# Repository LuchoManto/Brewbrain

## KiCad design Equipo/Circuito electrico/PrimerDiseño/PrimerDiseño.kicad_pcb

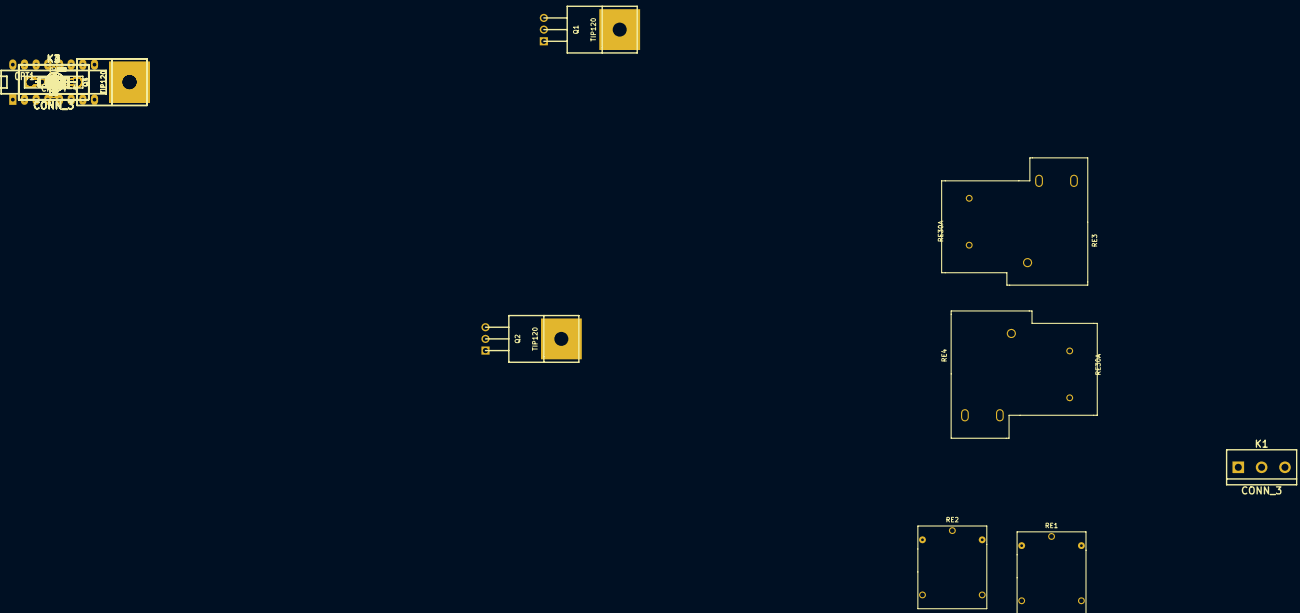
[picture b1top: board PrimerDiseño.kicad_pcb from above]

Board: 2 copper layers, 42 parts (0 on the bottom side), 31 nets, no tracks yet.

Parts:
D1, D2, D3, D4, D9, D10, D11, D12: LED; LED-3MM
D5, D6, D7, D8: DIODE; D3
K1, K2, K3, K4: CONN_3; bornier3
OPT1: CNY74-4; DIP-16__300_ELL
P1: CONN_5; PIN_ARRAY_5x1
Q1, Q2, Q3, Q4: TIP120; TO220
R1, R2, R3, R4: 50; R3
R5, R6, R7, R8: 470; R3
R9, R10, R11, R12, R15, R16, R17, R18: 1K; R3
RE1, RE2: RE
RE3, RE4: RE30A

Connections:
+5V: OPT1.10, OPT1.11, OPT1.14, OPT1.15
+12V: D5.2, D6.2, D7.2, D8.2, R15.1, R16.1, R17.1, R18.1
GND: D9.2, D10.2, D11.2, D12.2, P1.1, Q1.3, Q2.3, Q3.3, Q4.3, R1.1, R2.1, R3.1, R4.1, R5.2, R6.2, R7.2, R8.2
unnamed: D8.1, Q4.2
unnamed: D7.1, Q3.2
unnamed: D6.1, Q2.2
unnamed: D5.1, Q1.2
unnamed: D12.1, R18.2
unnamed: D1.2, R5.1
unnamed: D3.2, R7.1
unnamed: D2.2, R6.1
unnamed: OPT1.1, P1.5
unnamed: OPT1.4, P1.4
unnamed: OPT1.8, P1.2
unnamed: D11.1, R15.2
unnamed: D10.1, R17.2
unnamed: D9.1, R16.2
unnamed: D4.2, R8.1
unnamed: D4.1, Q4.1, R12.2
unnamed: D3.1, Q3.1, R11.2
unnamed: OPT1.6, R3.2
unnamed: OPT1.5, P1.3
unnamed: OPT1.3, R2.2
unnamed: OPT1.2, R1.2
unnamed: D2.1, Q2.1, R10.2
unnamed: OPT1.9, R12.1
unnamed: OPT1.16, R9.1
unnamed: OPT1.13, R10.1
unnamed: OPT1.12, R11.1
unnamed: OPT1.7, R4.2
unnamed: D1.1, Q1.1, R9.2

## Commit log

2017-04-07 primer commit
2017-04-07 primer borrador terminado
2017-04-20 asociados los componentes con los footprints. necesito asociar los pines de los modulos nuevos con las patas de los modulos esquematicos
